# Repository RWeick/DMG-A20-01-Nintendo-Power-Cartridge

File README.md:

# DMG-A20-01-Nintendo-Power-Cartridge
The Kicad files for the DMG-A20-01 Nintendo Power Cartridge for the Gameboy.

Thank you to [MSinger](https://github.com/msinger) for providing the board scans and performing testing to determine the purpose of various pins on the MMC and flash rom. 

PCB Thickness: 1.0 mm

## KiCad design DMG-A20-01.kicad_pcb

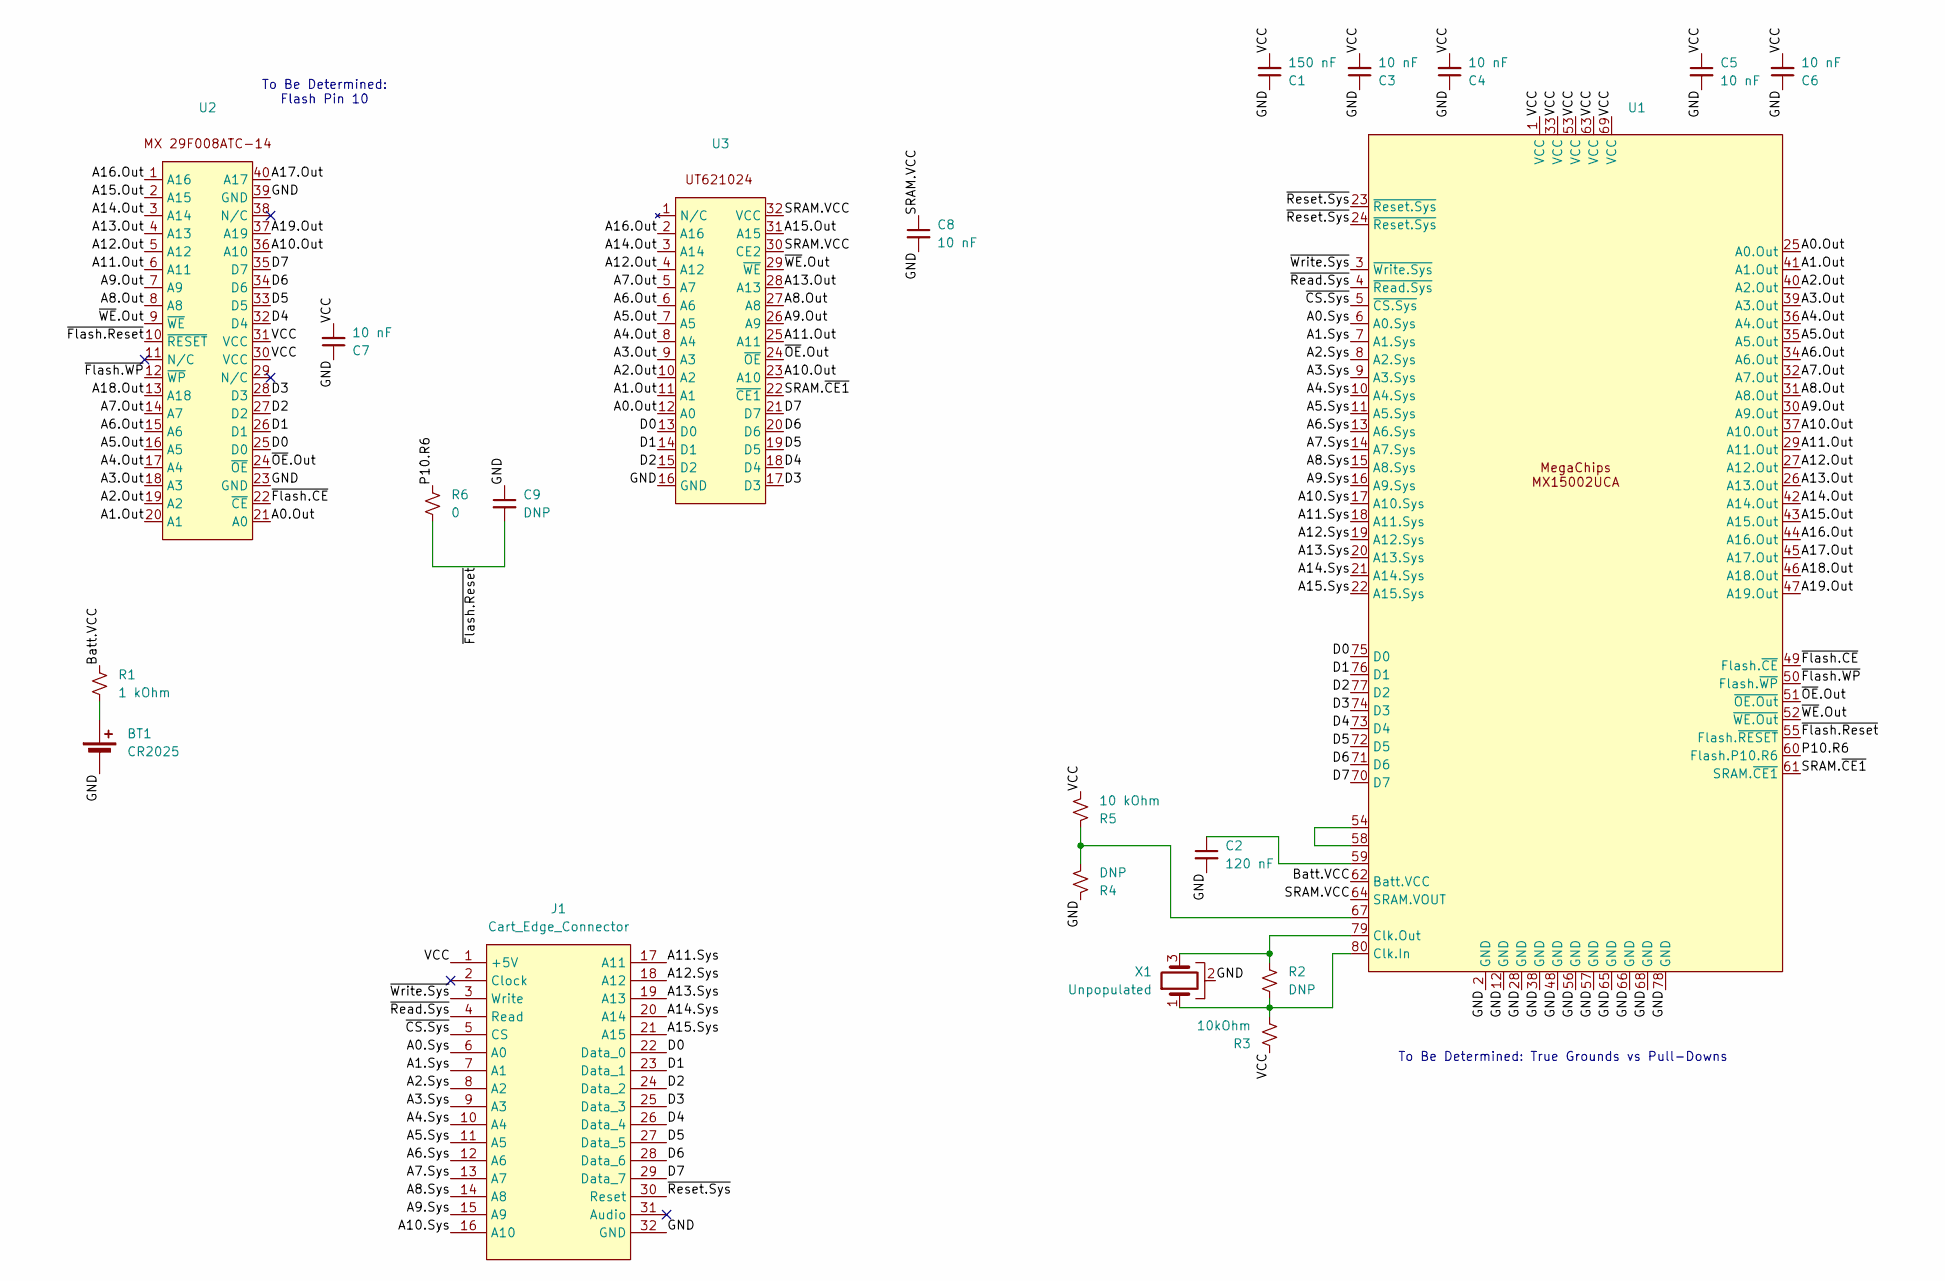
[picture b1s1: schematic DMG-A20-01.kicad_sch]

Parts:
BT1: CR2025; CR2025 Battery
C1: 150 nF; SMD Passive
C2: 120 nF; SMD Passive
C3, C4, C5, C6, C7, C8: 10 nF; SMD Passive
C9: DNP; SMD Passive
J1: Cart_Edge_Connector; Edge Connector
R1: 1 kOhm; SMD Passive
R2, R4: DNP; SMD Passive
R3: 10kOhm; SMD Passive
R5: 10 kOhm; SMD Passive
R6: 0; SMD Passive
U1: G-MMC1
U2: FLASH
U3: SRAM
X1: Unpopulated; Crystal

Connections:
/A0.Out: U1.25 (A0.Out), U2.21 (A0), U3.12 (A0)
/A0.Sys: J1.6 (A0), U1.6 (A0.Sys)
/A1.Out: U1.41 (A1.Out), U2.20 (A1), U3.11 (A1)
/A1.Sys: J1.7 (A1), U1.7 (A1.Sys)
/A2.Out: U1.40 (A2.Out), U2.19 (A2), U3.10 (A2)
/A2.Sys: J1.8 (A2), U1.8 (A2.Sys)
/A3.Out: U1.39 (A3.Out), U2.18 (A3), U3.9 (A3)
/A3.Sys: J1.9 (A3), U1.9 (A3.Sys)
/A4.Out: U1.36 (A4.Out), U2.17 (A4), U3.8 (A4)
/A4.Sys: J1.10 (A4), U1.10 (A4.Sys)
/A5.Out: U1.35 (A5.Out), U2.16 (A5), U3.7 (A5)
/A5.Sys: J1.11 (A5), U1.11 (A5.Sys)
/A6.Out: U1.34 (A6.Out), U2.15 (A6), U3.6 (A6)
/A6.Sys: J1.12 (A6), U1.13 (A6.Sys)
/A7.Out: U1.32 (A7.Out), U2.14 (A7), U3.5 (A7)
/A7.Sys: J1.13 (A7), U1.14 (A7.Sys)
/A8.Out: U1.31 (A8.Out), U2.8 (A8), U3.27 (A8)
/A8.Sys: J1.14 (A8), U1.15 (A8.Sys)
/A9.Out: U1.30 (A9.Out), U2.7 (A9), U3.26 (A9)
/A9.Sys: J1.15 (A9), U1.16 (A9.Sys)
/A10.Out: U1.37 (A10.Out), U2.36 (A10), U3.23 (A10)
/A10.Sys: J1.16 (A10), U1.17 (A10.Sys)
/A11.Out: U1.29 (A11.Out), U2.6 (A11), U3.25 (A11)
/A11.Sys: J1.17 (A11), U1.18 (A11.Sys)
/A12.Out: U1.27 (A12.Out), U2.5 (A12), U3.4 (A12)
/A12.Sys: J1.18 (A12), U1.19 (A12.Sys)
/A13.Out: U1.26 (A13.Out), U2.4 (A13), U3.28 (A13)
/A13.Sys: J1.19 (A13), U1.20 (A13.Sys)
/A14.Out: U1.42 (A14.Out), U2.3 (A14), U3.3 (A14)
/A14.Sys: J1.20 (A14), U1.21 (A14.Sys)
/A15.Out: U1.43 (A15.Out), U2.2 (A15), U3.31 (A15)
/A15.Sys: J1.21 (A15), U1.22 (A15.Sys)
/A16.Out: U1.44 (A16.Out), U2.1 (A16), U3.2 (A16)
/A17.Out: U1.45 (A17.Out), U2.40 (A17)
/A18.Out: U1.46 (A18.Out), U2.13 (A18)
/A19.Out: U1.47 (A19.Out), U2.37 (A19)
/Batt.VCC: R1.1, U1.62 (Batt.VCC)
/D0: J1.22 (Data_0), U1.75 (D0), U2.25 (D0), U3.13 (D0)
/D1: J1.23 (Data_1), U1.76 (D1), U2.26 (D1), U3.14 (D1)
/D2: J1.24 (Data_2), U1.77 (D2), U2.27 (D2), U3.15 (D2)
/D3: J1.25 (Data_3), U1.74 (D3), U2.28 (D3), U3.17 (D3)
/D4: J1.26 (Data_4), U1.73 (D4), U2.32 (D4), U3.18 (D4)
/D5: J1.27 (Data_5), U1.72 (D5), U2.33 (D5), U3.19 (D5)
/D6: J1.28 (Data_6), U1.71 (D6), U2.34 (D6), U3.20 (D6)
/D7: J1.29 (Data_7), U1.70 (D7), U2.35 (D7), U3.21 (D7)
/GND: BT1.2 (-), C1.1, C2.2, C3.1, C4.1, C5.2, C6.1, C7.1, C8.2, C9.1, J1.32 (GND), R4.1, U1.2 (GND), U1.12 (GND), U1.28 (GND), U1.38 (GND), U1.48 (GND), U1.56 (GND), U1.57 (GND), U1.65 (GND), U1.66 (GND), U1.68 (GND), U1.78 (GND), U2.23 (GND), U2.39 (GND), U3.16 (GND), X1.2
/P10.R6: R6.1, U1.60 (Flash.P10.R6)
/SRAM.VCC: C8.1, U1.64 (SRAM.VOUT), U3.30 (CE2), U3.32 (VCC)
/SRAM.~CE1: U1.61 (SRAM.~CE1), U3.22 (~CE1)
/VCC: C1.2, C3.2, C4.2, C5.1, C6.2, C7.2, J1.1 (+5V), R3.1, R5.2, U1.1 (VCC), U1.33 (VCC), U1.53 (VCC), U1.63 (VCC), U1.69 (VCC), U2.30 (VCC), U2.31 (VCC)
/~CS.Sys: J1.5 (CS), U1.5 (~CS.Sys)
/~Flash.CE: U1.49 (Flash.~CE), U2.22 (~CE)
/~Flash.Reset: C9.2, R6.2, U1.55 (Flash.~RESET), U2.10 (~RESET)
/~Flash.WP: U1.50 (Flash.~WP), U2.12 (~WP)
/~OE.Out: U1.51 (~OE.Out), U2.24 (~OE), U3.24 (~OE)
/~Read.Sys: J1.4 (Read), U1.4 (~Read.Sys)
/~Reset.Sys: J1.30 (Reset), U1.23 (~Reset.Sys), U1.24 (~Reset.Sys)
/~WE.Out: U1.52 (~WE.Out), U2.9 (~WE), U3.29 (~WE)
/~Write.Sys: J1.3 (Write), U1.3 (~Write.Sys)
unnamed: BT1.1 (+), R1.2
unnamed: C2.1, U1.59
unnamed: R4.2, R5.1, U1.67
unnamed: R2.1, R3.2, U1.80 (Clk.In), X1.1
unnamed: R2.2, U1.79 (Clk.Out), X1.3
unnamed: U1.54, U1.58

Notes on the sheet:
To Be Determined: True Grounds vs Pull-Downs
To Be Determined: Flash Pin 10

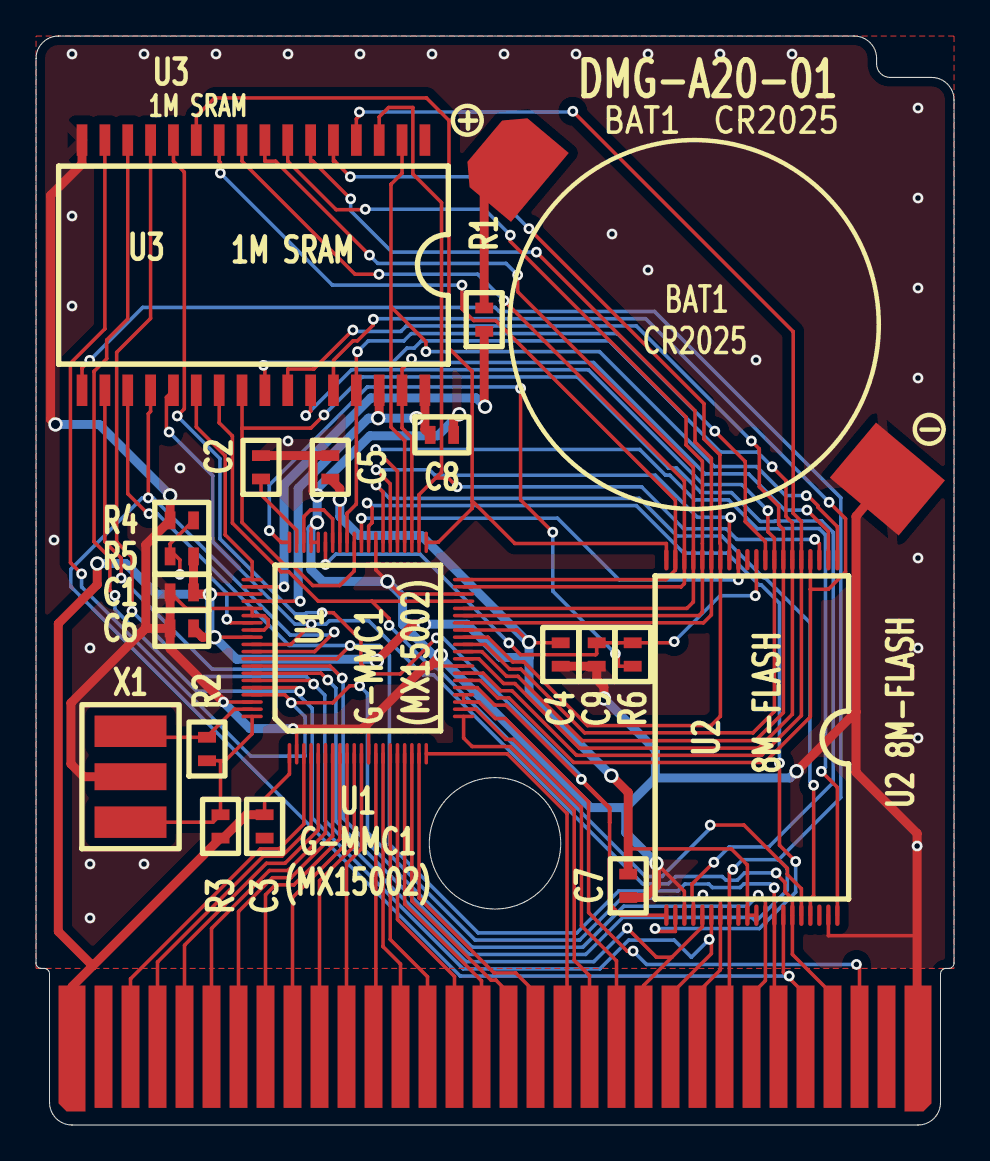
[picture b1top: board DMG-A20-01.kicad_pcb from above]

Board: 2 copper layers, 51.0 x 60.5 mm, 22 parts (0 on the bottom side), 65 nets.

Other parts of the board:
Hole: MountingHole_8.4mm_M8
